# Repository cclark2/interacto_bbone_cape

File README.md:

Interacto BeagleBone Cape
=========================

Get your BeagleBone interactive with a triple axis accelerometer, gyroscope, and magnetometer, plus a 640x480 30fps camera! All sensors are digital and communicate via I2C to the BeagleBone. The camera frames are captured using the PRU.

Special thanks to <a href="http://www.sparkfun.com/">SparkFun</a> for use of their open-source EAGLE libraries.

## Project Links
- <a href="http://www.hitchhikeree.org/beaglebone_capes/interacto/">HitchhikerEE page</a>
- <a href="http://www.youtube.com/watch?v=t2w74zxGNqg">YouTube video</a>
- <a href="https://docs.google.com/folder/d/0B5HjtPsFD8u5ZUltQlZ1RDNVN1U/edit">Design files on Google Drive</a>
- <a href="http://beagleboard.org/CapeContest/entries/Interacto/">BeagleBone Cape Contest page</a>

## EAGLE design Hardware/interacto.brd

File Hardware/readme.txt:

Might be a good idea to go with OVM7690-R20A for the camera instead.
It's cheaper, probably more available, and has the same interface as the current part.

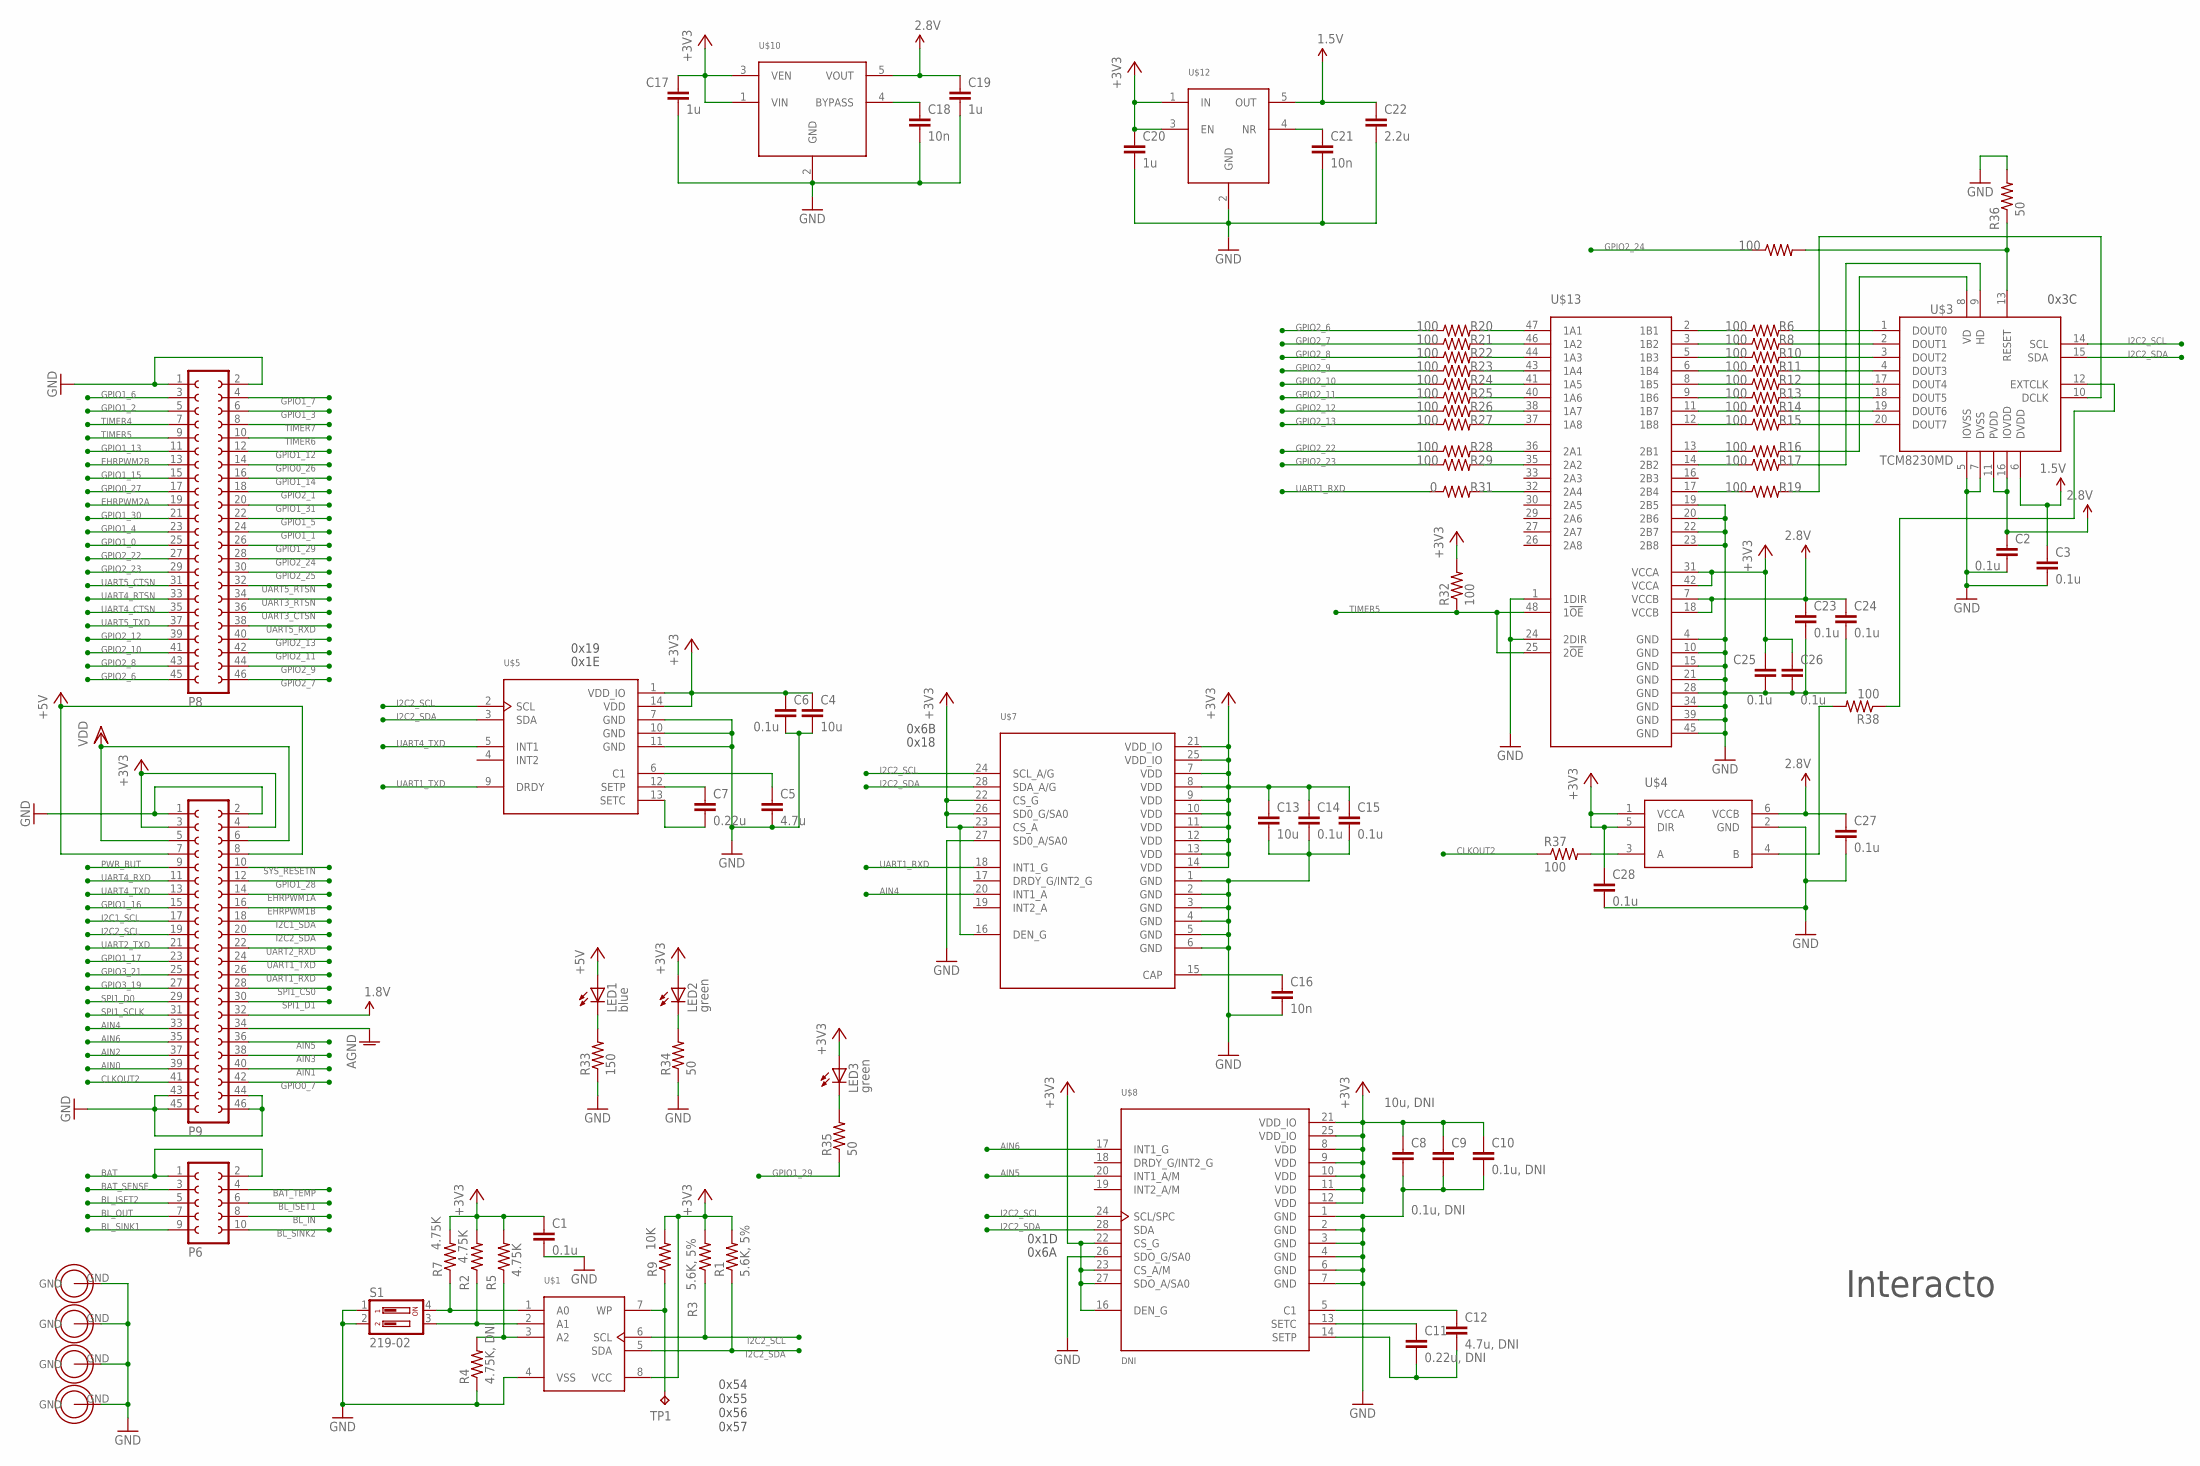
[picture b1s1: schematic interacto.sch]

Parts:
C1, C2, C3, C6, C14, C15, C23, C24, C25, C26, C27, C28: 0.1u; C0603; MPN VJ0603V104ZXXCW1BC
C4, C13: 10u; C0603; MPN LMK107BBJ106MALT
C5: 4.7u; C0603; MPN GRM188F51A475ZE20J
C7: 0.22u; C0603; MPN VJ0603V224MXJPW1BC
C8: 10u, DNI; C0603; MPN LMK107BBJ106MALT
C9, C10: 0.1u, DNI; C0603; MPN VJ0603V104ZXXCW1BC
C11: 0.22u, DNI; C0603; MPN VJ0603V224MXJPW1BC
C12: 4.7u, DNI; C0603; MPN GRM188F51A475ZE20J
C16, C18, C21: 10n; C0603; MPN VJ0603Y103KXACW1BC
C17, C19, C20: 1u; C0603; MPN C1608X7R1C105K
C22: 2.2u; C0603; MPN C1608Y5V1C225Z
H1, H2, H3, H4: HOLE
LED1: blue; CHIPLED_0603; MPN HT-193NB-5589
LED2, LED3: green; CHIPLED_0603; MPN LG Q971-KN-1
P6: FE05-2; MPN SSHQ-105-D-10-GT-LF
P8, P9: FE23-2; MPN SSHQ-123-D-10-GT-LF
R1, R3: 5.6K, 5%; R0603; MPN RK73B1JTTDD562J
R2, R5, R7: 4.75K; R0603; MPN CR0603-FX-4751GLF
R4: 4.75K, DNI; R0603; MPN CR0603-FX-4751GLF
R6, R8, R10, R11, R12, R13, R14, R15, R16, R17, R18, R19, R20, R21, R22, R23, R24, R25, R26, R28, R29, R32, R37, R38: 100; R0402; MPN ERA-6AED101V
R9: 10K; R0603; MPN WR06X1002FTL
R27: 100; R0402; MPN CR0402-JW-330GLF
R31: 0; R0402; MPN ERJ-2GE0R00X
R33: 150; R0603; MPN 302-150-RC
R34, R35: 50; R0603; MPN 302-49.9-RC
R36: 50; R0402; MPN 302-49.9-RC
S1: 219-02; CTS-219-02; MPN 219-2MST
TP1: TPB2,54; B2,54
U$1: CAT24C256; SOIC8; MPN CAT24C256WI-GT3
U$3: TCM8230MD; MPN TCM8230MD
U$4: SN74LVC1T45; SOT23-6; MPN SN74LVC1T45DBVR
U$5: LSM303DLHC; LGA14; MPN LSM303DLHC
U$7: LSM330DLC; LGA28-4X5; MPN LSM330DLC
U$8: DNI; LGA28; MPN LSM333D
U$10: LP3985; SOT23-5; MPN LP3985IM5-2.8/NOPB
U$12: TPS799XX; SOT23-5; MPN TPS79915DDCR
U$13: SN74LVCH16T245; TSSOP48; MPN SN74LVCH16T245DGGR

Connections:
1.5V: C3.1, C22.1, U$3.6 (DVDD), U$12.5 (OUT)
1.8V: P9.32
2.85V: C2.1, C19.1, C23.1, C24.1, C27.1, U$3.11 (PVDD), U$3.16 (IOVDD), U$4.6 (VCCB), U$10.5 (VOUT), U$13.7 (VCCB), U$13.18 (VCCB)
+3V3: C1.1, C4.1, C6.1, C8.1, C9.1, C10.1, C13.1, C14.1, C15.1, C17.1, C20.1, C25.1, C26.1, C28.1, LED2.A, LED3.A, P9.3, P9.4, R1.2, R2.2, R3.2, R5.2, R7.2, R9.2, R32.2, U$1.8 (VCC), U$4.1 (VCCA), U$4.5 (DIR), U$5.1 (VDD_IO), U$5.14 (VDD), U$7.7 (VDD), U$7.8 (VDD), U$7.9 (VDD), U$7.10 (VDD), U$7.11 (VDD), U$7.12 (VDD), U$7.13 (VDD), U$7.14 (VDD), U$7.16 (DEN_G), U$7.21 (VDD_IO), U$7.22 (CS_G), U$7.23 (CS_A), U$7.25 (VDD_IO), U$7.26 (SD0_G/SA0), U$8.8 (VDD), U$8.9 (VDD), U$8.10 (VDD), U$8.11 (VDD), U$8.12 (VDD), U$8.16 (DEN_G), U$8.21 (VDD_IO), U$8.22 (CS_G), U$8.23 (CS_A/M), U$8.25 (VDD_IO), U$8.27 (SDO_A/SA0), U$10.1 (VIN), U$10.3 (VEN), U$12.1 (IN), U$12.3 (EN), U$13.31 (VCCA), U$13.42 (VCCA)
+5V: LED1.A, P9.7, P9.8
AGND: P9.34
AIN0: P9.39
AIN1: P9.40
AIN2: P9.37
AIN3: P9.38
AIN4: P9.33, U$7.20 (INT1_A)
AIN5: P9.36, U$8.20 (INT1_A/M)
AIN6: P9.35, U$8.17 (INT1_G)
BAT: P6.1, P6.2
BAT_SENSE: P6.3
BAT_TEMP: P6.4
BL_IN: P6.8
BL_ISET1: P6.6
BL_ISET2: P6.5
BL_OUT: P6.7
BL_SINK1: P6.9
BL_SINK2: P6.10
CLKOUT2: P9.41, R37.1
EHRPWM1A: P9.14
EHRPWM1B: P9.16
EHRPWM2A: P8.19
EHRPWM2B: P8.13
GND: C1.2, C2.2, C3.2, C4.2, C5.2, C6.2, C8.2, C9.2, C10.2, C13.2, C14.2, C15.2, C16.2, C17.2, C18.2, C19.2, C20.2, C21.2, C22.2, C23.2, C24.2, C25.2, C26.2, C27.2, C28.2, H1.GND, H2.GND, H3.GND, H4.GND, P8.1, P8.2, P9.1, P9.2, P9.43, P9.44, P9.45, P9.46, R4.1, R33.1, R34.1, R36.2, S1.1, S1.2, U$1.4 (VSS), U$3.5 (IOVSS), U$3.7 (DVSS), U$4.2 (GND), U$5.7 (GND), U$5.10 (GND), U$5.11 (GND), U$7.1 (GND), U$7.2 (GND), U$7.3 (GND), U$7.4 (GND), U$7.5 (GND), U$7.6 (GND), U$7.27 (SD0_A/SA0), U$8.1 (GND), U$8.2 (GND), U$8.3 (GND), U$8.4 (GND), U$8.6 (GND), U$8.7 (GND), U$8.26 (SDO_G/SA0), U$10.2 (GND), U$12.2 (GND), U$13.1 (1DIR), U$13.4 (GND), U$13.10 (GND), U$13.15 (GND), U$13.19 (2B5), U$13.20 (2B6), U$13.21 (GND), U$13.22 (2B7), U$13.23 (2B8), U$13.24 (2DIR), U$13.28 (GND), U$13.34 (GND), U$13.39 (GND), U$13.45 (GND)
GPIO0_7: P9.42
GPIO0_26: P8.14
GPIO0_27: P8.17
GPIO1_0: P8.25
GPIO1_1: P8.24
GPIO1_2: P8.5
GPIO1_3: P8.6
GPIO1_4: P8.23
GPIO1_5: P8.22
GPIO1_6: P8.3
GPIO1_7: P8.4
GPIO1_12: P8.12
GPIO1_13: P8.11
GPIO1_14: P8.16
GPIO1_15: P8.15
GPIO1_16: P9.15
GPIO1_17: P9.23
GPIO1_28: P9.12
GPIO1_29: P8.26, R35.1
GPIO1_30: P8.21
GPIO1_31: P8.20
GPIO2_1: P8.18
GPIO2_6: P8.45, R20.1
GPIO2_7: P8.46, R21.1
GPIO2_8: P8.43, R22.1
GPIO2_9: P8.44, R23.1
GPIO2_10: P8.41, R24.1
GPIO2_11: P8.42, R25.1
GPIO2_12: P8.39, R26.1
GPIO2_13: P8.40, R27.1
GPIO2_22: P8.27, R28.1
GPIO2_23: P8.29, R29.1
GPIO2_24: P8.28, R18.1
GPIO2_25: P8.30
GPIO3_19: P9.27
GPIO3_21: P9.25
I2C1_SCL: P9.17
I2C1_SDA: P9.18
I2C2_SCL: P9.19, R3.1, U$1.6 (SCL), U$3.14 (SCL), U$5.2 (SCL), U$7.24 (SCL_A/G), U$8.24 (SCL/SPC)
I2C2_SDA: P9.20, R1.1, U$1.5 (SDA), U$3.15 (SDA), U$5.3 (SDA), U$7.28 (SDA_A/G), U$8.28 (SDA)
unnamed: R7.1, S1.4, U$1.1 (A0)
unnamed: R2.1, S1.3, U$1.2 (A1)
unnamed: R4.2, R5.1, U$1.3 (A2)
unnamed: R6.1, U$13.2 (1B1)
unnamed: R9.1, TP1.TP, U$1.7 (WP)
unnamed: R8.1, U$13.3 (1B2)
unnamed: R10.1, U$13.5 (1B3)
unnamed: R11.1, U$13.6 (1B4)
unnamed: R12.1, U$13.8 (1B5)
unnamed: R13.1, U$13.9 (1B6)
unnamed: R14.1, U$13.11 (1B7)
unnamed: R15.1, U$13.12 (1B8)
unnamed: R19.2, U$3.10 (DCLK)
unnamed: R16.2, U$3.8 (VD)
unnamed: R17.2, U$3.9 (HD)
unnamed: R18.2, R36.1, U$3.13 (RESET)
unnamed: R28.2, U$13.36 (2A1)
unnamed: LED1.C, R33.2
unnamed: LED2.C, R34.2
unnamed: R16.1, U$13.13 (2B1)
unnamed: R17.1, U$13.14 (2B2)
unnamed: R19.1, U$13.17 (2B4)
unnamed: R6.2, U$3.1 (DOUT0)
unnamed: R8.2, U$3.2 (DOUT1)
unnamed: R10.2, U$3.3 (DOUT2)
unnamed: R11.2, U$3.4 (DOUT3)
unnamed: R12.2, U$3.17 (DOUT4)
unnamed: R13.2, U$3.18 (DOUT5)
unnamed: R14.2, U$3.19 (DOUT6)
unnamed: R15.2, U$3.20 (DOUT7)
unnamed: R20.2, U$13.47 (1A1)
unnamed: R21.2, U$13.46 (1A2)
unnamed: R22.2, U$13.44 (1A3)
unnamed: R23.2, U$13.43 (1A4)
unnamed: R24.2, U$13.41 (1A5)
unnamed: R25.2, U$13.40 (1A6)
unnamed: R26.2, U$13.38 (1A7)
unnamed: R27.2, U$13.37 (1A8)
unnamed: R29.2, U$13.35 (2A2)
unnamed: R31.2, U$13.32 (2A4)
unnamed: LED3.C, R35.2
unnamed: C7.1, U$5.12 (SETP)
unnamed: C7.2, U$5.13 (SETC)
unnamed: C5.1, U$5.6 (C1)
unnamed: C16.1, U$7.15 (CAP)
unnamed: C11.1, U$8.13 (SETC)
unnamed: C11.2, C12.2, U$8.14 (SETP)
unnamed: C12.1, U$8.5 (C1)
unnamed: C18.1, U$10.4 (BYPASS)
unnamed: R38.1, U$3.12 (EXTCLK)
unnamed: R37.2, U$4.3 (A)
unnamed: C21.1, U$12.4 (NR)
unnamed: R38.2, U$4.4 (B)
PWR_BUT: P9.9
SPI1_CS0: P9.28
SPI1_D0: P9.29
SPI1_D1: P9.30
SPI1_SCLK: P9.31
SYS_RESETN: P9.10
TIMER4: P8.7
TIMER5: P8.9, R32.1, U$13.25 (2!OE), U$13.48 (1!OE)
TIMER6: P8.10
TIMER7: P8.8
UART1_RXD: P9.26, R31.1, U$7.18 (INT1_G)
UART1_TXD: P9.24, U$5.9 (DRDY)
UART2_RXD: P9.22
UART2_TXD: P9.21
UART3_CTSN: P8.36
UART3_RTSN: P8.34
UART4_CTSN: P8.35
UART4_RTSN: P8.33
UART4_RXD: P9.11
UART4_TXD: P9.13, U$5.5 (INT1)
UART5_CTSN: P8.31
UART5_RTSN: P8.32
UART5_RXD: P8.38
UART5_TXD: P8.37
VDD: P9.5, P9.6

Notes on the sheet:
Interacto
0x54 0x55 0x56 0x57
0x19
0x1E
0x18
0x6B
0x1D
0x6A
0x3C

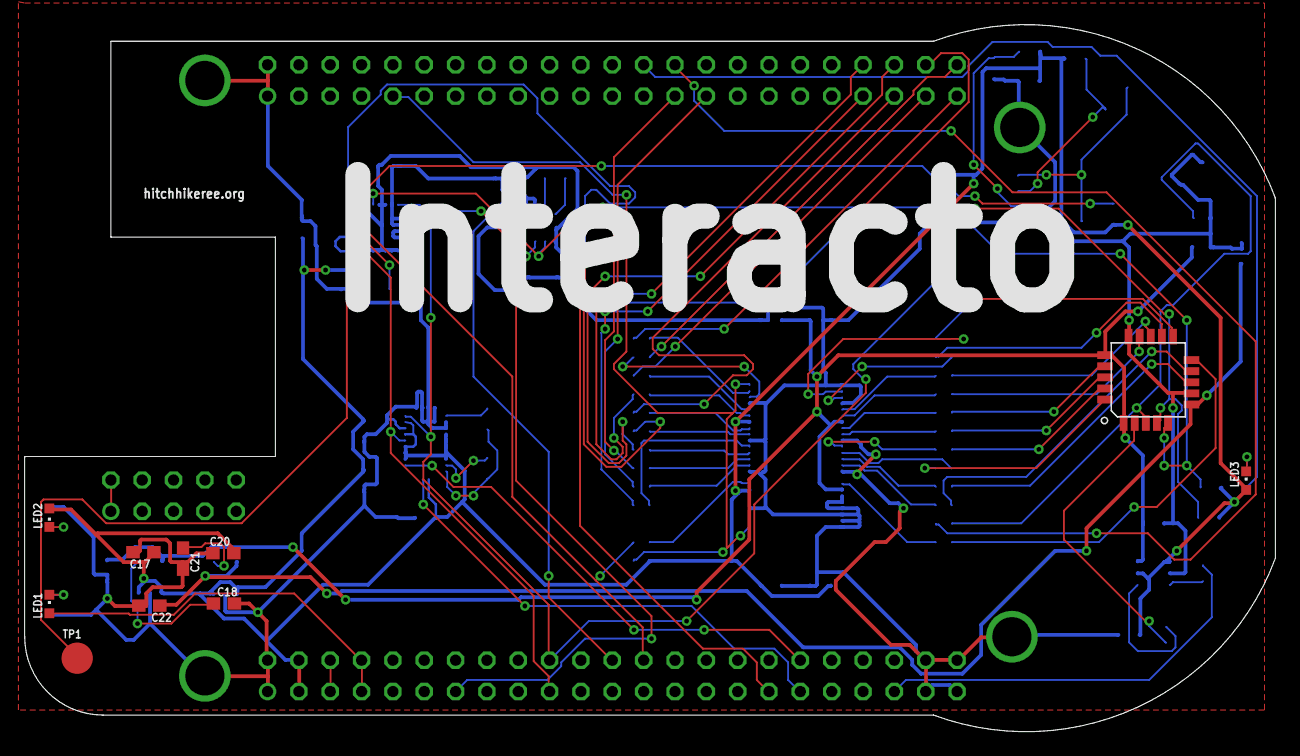
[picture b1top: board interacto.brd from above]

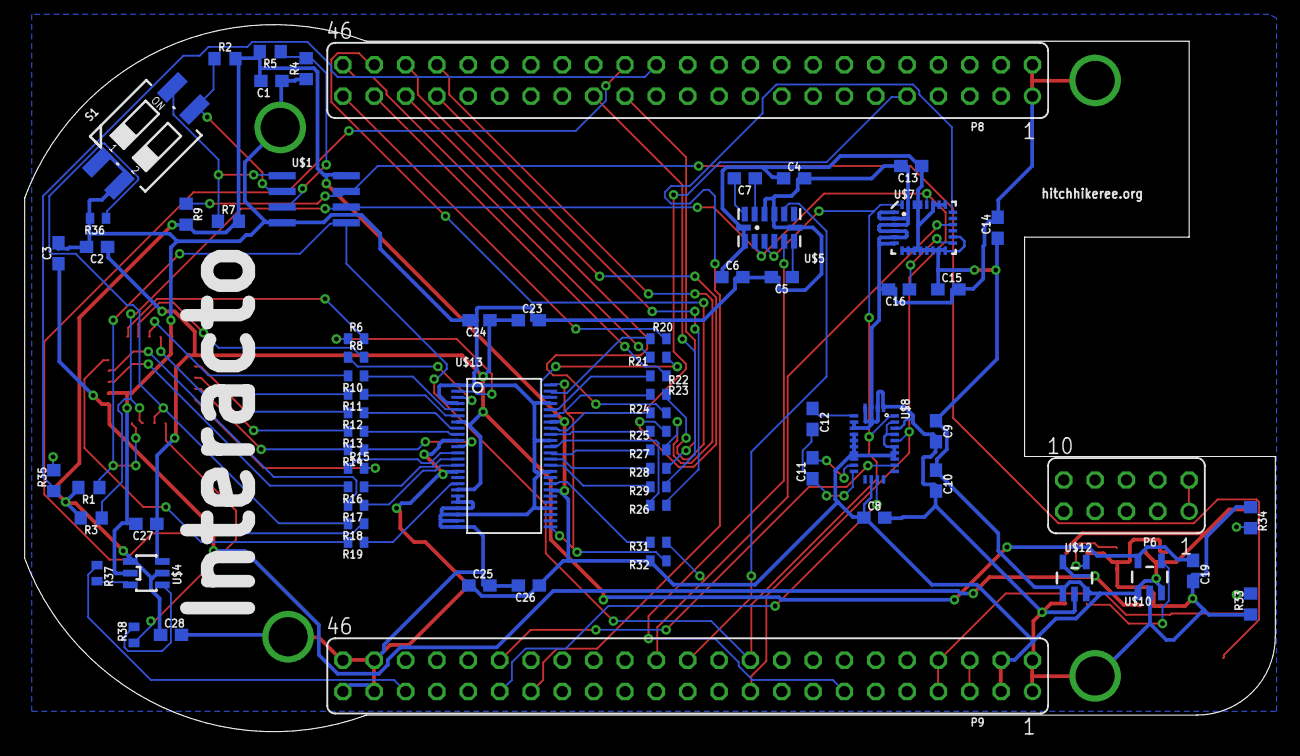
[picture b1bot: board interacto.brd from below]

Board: 2 copper layers, 101.4 x 57.3 mm, 86 parts (72 on the bottom side), 82 nets.

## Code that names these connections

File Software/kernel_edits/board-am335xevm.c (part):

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	{"mcasp0_axr0.gpio3_16",    OMAP_MUX_MODE7 | AM33XX_PIN_INPUT}, //down
	{"mcasp0_fsr.gpio3_19",    OMAP_MUX_MODE7 | AM33XX_PIN_OUTPUT}, // DISEN
	{"gpmc_ben1.gpio1_28",    OMAP_MUX_MODE7 | AM33XX_PIN_OUTPUT}, // LED1
	{"uart1_txd.gpio0_15", OMAP_MUX_MODE7 | AM33XX_PIN_INPUT}, // ENTER
	{"uart1_rxd.gpio0_14", OMAP_MUX_MODE7 | AM33XX_PIN_INPUT}, // TSC_INT
	{NULL, 0},
};

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	{"gpmc_ad0.mmc1_dat0",	OMAP_MUX_MODE1 | AM33XX_PIN_INPUT_PULLUP},
	{"gpmc_csn1.mmc1_clk",	OMAP_MUX_MODE2 | AM33XX_PIN_INPUT_PULLUP},
	{"gpmc_csn2.mmc1_cmd",	OMAP_MUX_MODE2 | AM33XX_PIN_INPUT_PULLUP},
	{"gpmc_csn0.gpio1_29",	OMAP_MUX_MODE7 | AM33XX_PIN_INPUT_PULLUP},
	{"gpmc_advn_ale.mmc1_sdcd", OMAP_MUX_MODE7 | AM33XX_PIN_INPUT_PULLUP},
	{"uart1_rxd.mmc1_sdwp", OMAP_MUX_MODE1 | AM33XX_PIN_INPUT_PULLDOWN},
	{NULL, 0},
};

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};

static struct pinmux_config tt3201_pin_mux[] = {
	{"uart1_rxd.d_can1_tx", OMAP_MUX_MODE2 | AM33XX_PIN_OUTPUT },
	{"uart1_txd.d_can1_rx", OMAP_MUX_MODE2 | AM33XX_PIN_INPUT_PULLUP },
	{"mcasp0_fsr.gpio3_19", OMAP_MUX_MODE7 | AM33XX_PIN_INPUT_PULLUP },
	{"mcasp0_ahclkx.gpio3_21", OMAP_MUX_MODE7 | AM33XX_PIN_INPUT_PULLUP },
	{"ecap0_in_pwm0_out.spi1_cs1", OMAP_MUX_MODE2 | AM33XX_PIN_OUTPUT_PULLUP },
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};

static struct pinmux_config uart1dcan1_pin_mux[] = {
	{"uart1_rxd.d_can1_tx", OMAP_MUX_MODE2 | AM33XX_PIN_OUTPUT },
	{"uart1_txd.d_can1_rx", OMAP_MUX_MODE2 | AM33XX_PIN_INPUT_PULLUP },
	{NULL, 0},
};

static struct pinmux_config uart1_pin_mux[] = {
	{"uart1_txd.uart1_txd", OMAP_MUX_MODE0 | AM33XX_PULL_ENBL},
	{"uart1_rxd.uart1_rxd", OMAP_MUX_MODE0 | AM33XX_PIN_INPUT_PULLUP},
	{NULL, 0},
};

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
/* pinmux for profibus */
static struct pinmux_config profibus_pin_mux[] = {
	{"uart1_rxd.pr1_uart0_rxd_mux1", OMAP_MUX_MODE5 | AM33XX_PIN_INPUT},
	{"uart1_txd.pr1_uart0_txd_mux1", OMAP_MUX_MODE5 | AM33XX_PIN_OUTPUT},
	{"mcasp0_fsr.pr1_pru0_pru_r30_5", OMAP_MUX_MODE5 | AM33XX_PIN_OUTPUT},
	{NULL, 0},
};
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static struct pinmux_config uart1_wl12xx_pin_mux[] = {
	{"uart1_ctsn.uart1_ctsn", OMAP_MUX_MODE0 | AM33XX_PIN_OUTPUT},
	{"uart1_rtsn.uart1_rtsn", OMAP_MUX_MODE0 | AM33XX_PIN_INPUT},
	{"uart1_rxd.uart1_rxd", OMAP_MUX_MODE0 | AM33XX_PIN_INPUT_PULLUP},
	{"uart1_txd.uart1_txd", OMAP_MUX_MODE0 | AM33XX_PULL_ENBL},
	{NULL, 0},
};
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
/* Enable clkout2 */
static struct pinmux_config clkout2_pin_mux[] = {
	{"xdma_event_intr1.clkout2", OMAP_MUX_MODE3 | AM33XX_PIN_OUTPUT},
	{NULL, 0},
};

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
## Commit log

2013-01-01 Design complete, cleanup needed.
2013-01-01 BOM done.
2013-01-06 Adding BOM prices, adding PDFs of design, sorting files, adding software.
2013-03-18 Updates from prototype build and testing.

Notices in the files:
Software/kernel_edits/board-am335xevm.c:
Copyright (C) 2011 Texas Instruments, Inc. - http://www.ti.com
modify it under the terms of the GNU General Public License as
published by the Free Software Foundation version 2.
